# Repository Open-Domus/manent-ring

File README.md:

# Manent ring: hardware

Hardware design of the Manent ring: a ring with one button that records what you say
and hands it to your phone over Bluetooth LE. Firmware and radio protocol live in the
`mnemo-band` repository; the public description is the `manent-site` repository.

Public page: [manentlabs.it/en/](https://manentlabs.it/en/) (English), [manentlabs.it/](https://manentlabs.it/) (Italian).

Nothing here has been built or measured. This is a design on paper, checked by scripts.

| What | Where |
| --- | --- |
| Design document: requirements, architecture, decisions | [docs/design.md](docs/design.md) |
| Does it fit? Envelope, islands, cell, ring sizes | [docs/space-budget.md](docs/space-budget.md) |
| How long does it last? | [docs/power-budget.md](docs/power-budget.md) |
| How does it charge? Contacts, dock, why not wireless | [docs/charging.md](docs/charging.md) |
| What is unknown, and what would settle it | [docs/open-questions.md](docs/open-questions.md) |
| Parts with sizes and how far each is verified | [parts/parts.yaml](parts/parts.yaml) |
| Circuit, as data | [electrical/gen/design.py](electrical/gen/design.py) |
| Schematic (KiCad 10), PDF, netlist, bill of materials | `electrical/kicad/`, `electrical/out/` |
| Board: placed and routed (connectivity proof, not a fabrication layout) | `electrical/kicad/manent.kicad_pcb`, `electrical/out/board-*.svg` |
| Charging dock, printable, one per ring size | `mechanical/manent_mech/dock.py`, `mechanical/out/print-dock-*.stl` |
| Fit model, drawings, STEP, STL to 3D print | `mechanical/`, `mechanical/out/` |
| Quote request for a fabricator | [quote/request.md](quote/request.md); `make quote` builds the zip to send |

## Build

Needs `uv`, and either KiCad 10 or Docker (`docker pull kicad/kicad:10.0`).

```
make all        # schematic, board, checks, tests, fit report, drawings, budgets, STEP
make test       # tests only
make route      # route the board again from scratch (several minutes; it may not finish every time)
```

The schematic and the board are generated: edit `electrical/gen/design.py` and the fit
model, never the `.kicad_sch` or `.kicad_pcb` files.
Every pin carries a label with its net name instead of drawn wires. `make schematic` runs
KiCad's rule check and compares the netlist KiCad reads with the one in `design.py`.

## Licences

Following the proposal on the product site: hardware under CERN-OHL-S v2 (`LICENSE`),
documents under CC BY-SA 4.0 (`LICENSE-docs`). The licence of the scripts is not decided.

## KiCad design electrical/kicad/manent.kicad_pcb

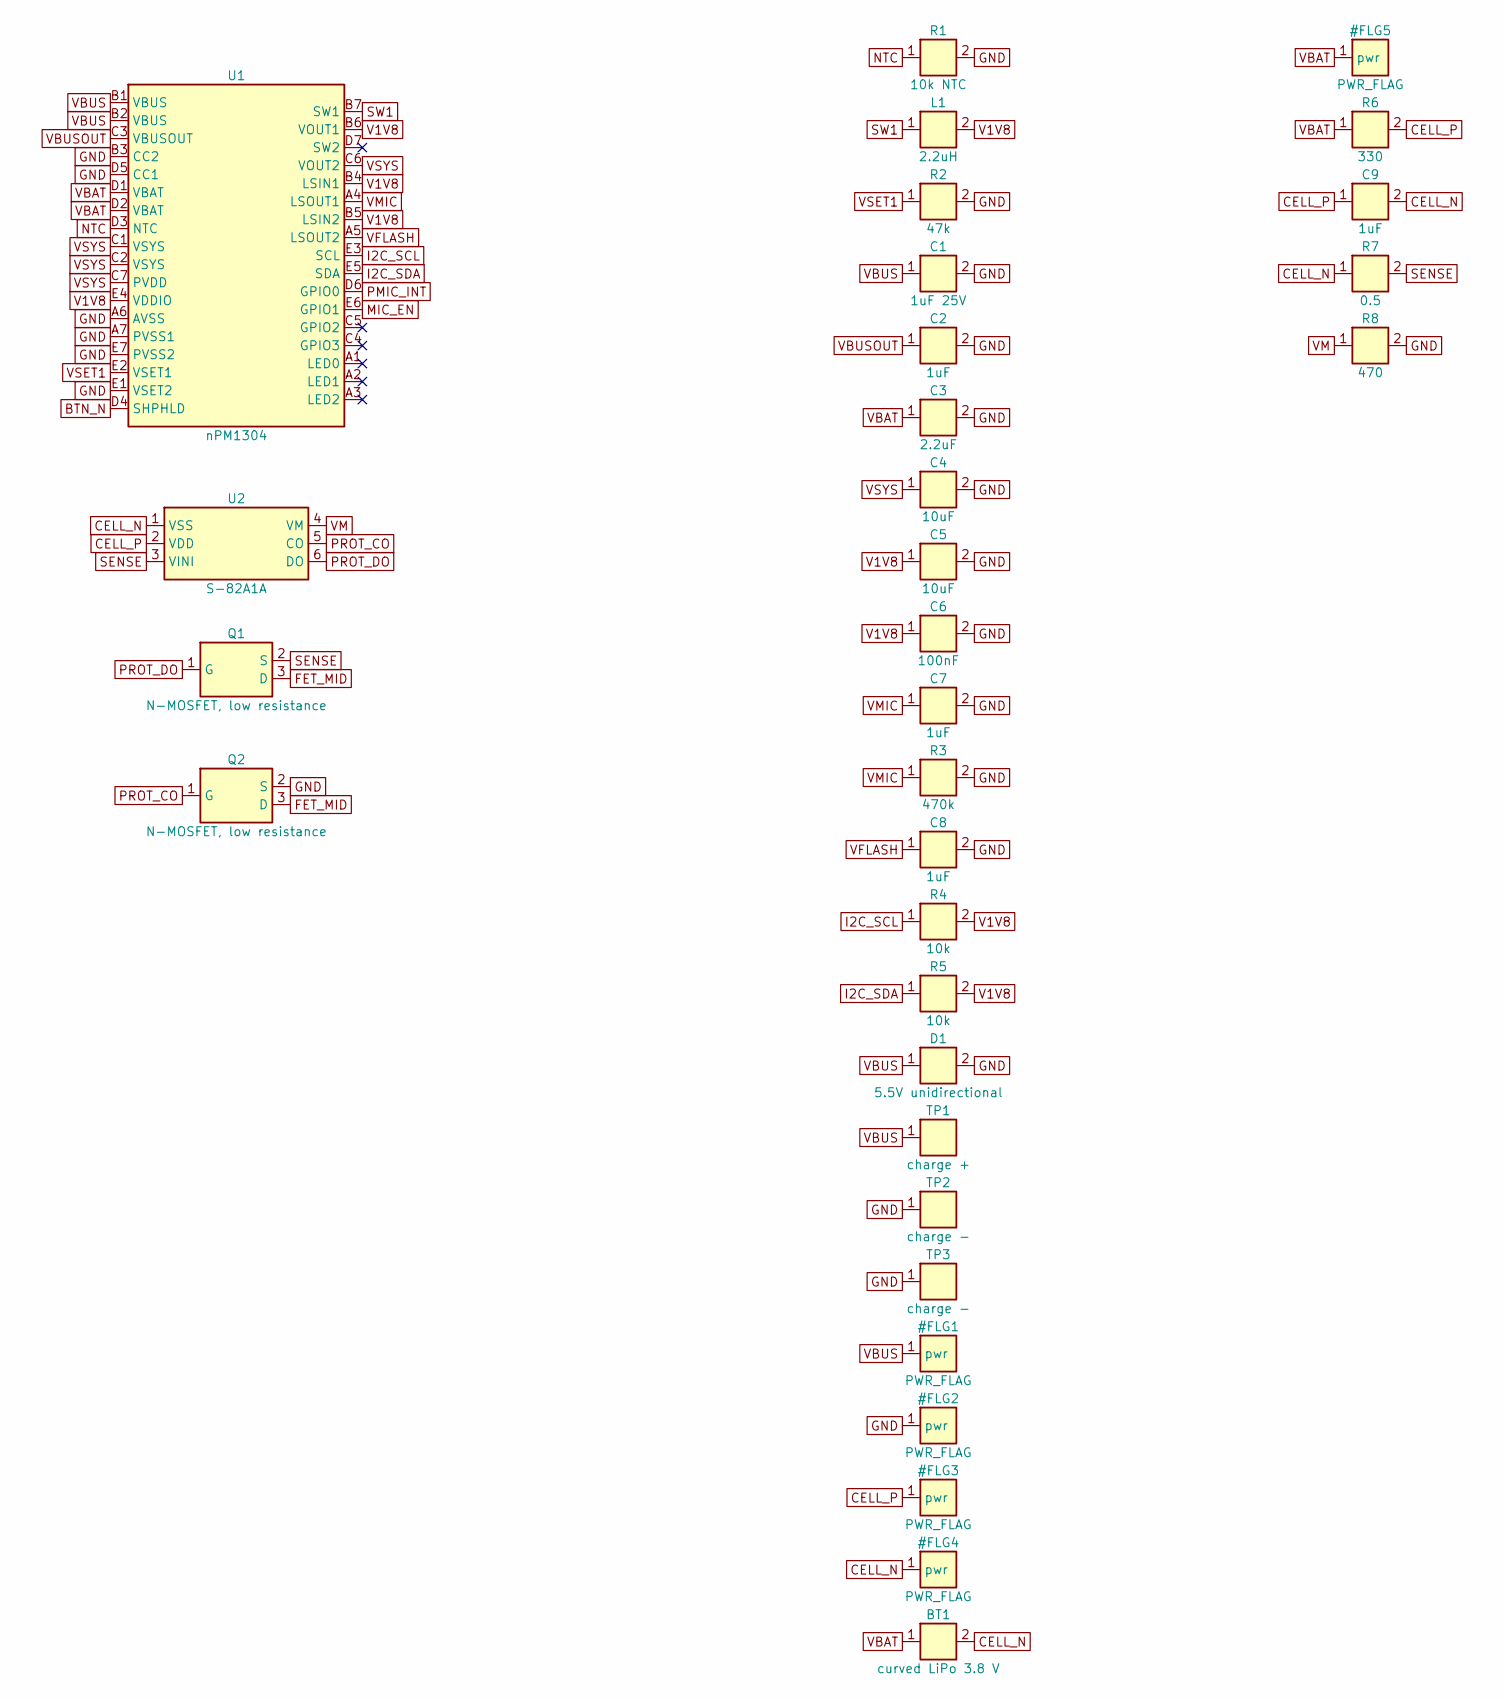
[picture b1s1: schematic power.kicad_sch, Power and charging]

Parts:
BT1: curved LiPo 3.8 V; Cell_Tabs; MPN GRP1707xx / GRP160626
C1: 1uF 25V; C_0402_1005Metric
C2, C7, C8, C9: 1uF; C_0201_0603Metric
C3: 2.2uF; C_0402_1005Metric
C4, C5: 10uF; C_0402_1005Metric
C6: 100nF; C_0201_0603Metric
D1: 5.5V unidirectional; D_0201_0603Metric; MPN to choose
L1: 2.2uH; L_0603_1608Metric; MPN to choose
Q1, Q2: N-MOSFET, low resistance; SOT-883; MPN PMZB290UNE2
R1: 10k NTC; R_0201_0603Metric
R2: 47k; R_0201_0603Metric
R3: 470k; R_0201_0603Metric
R4, R5: 10k; R_0201_0603Metric
R6: 330; R_0201_0603Metric
R7: 0.5; R_0201_0603Metric
R8: 470; R_0201_0603Metric
TP1: charge +; Pad_Charge_D1.5
TP2, TP3: charge -; Pad_Charge_D1.5
U1: nPM1304; nPM1304_CSP35; MPN nPM1304-CAAA-R
U2: S-82A1A; DFN-6_1414; MPN S-82A1AAG-A6T5S (variant to confirm)

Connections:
BTN_N: U1.D4 (SHPHLD); also elsewhere on the board
CELL_N: BT1.2, C9.2, R7.1, U2.1 (VSS)
CELL_P: C9.1, R6.2, U2.2 (VDD)
FET_MID: Q1.3 (D), Q2.3 (D)
GND: C1.2, C2.2, C3.2, C4.2, C5.2, C6.2, C7.2, C8.2, D1.2, Q2.2 (S), R1.2, R2.2, R3.2, R8.2, TP2.1, TP3.1, U1.A6 (AVSS), U1.A7 (PVSS1), U1.B3 (CC2), U1.D5 (CC1), U1.E1 (VSET2), U1.E7 (PVSS2); also elsewhere on the board
I2C_SCL: R4.1, U1.E3 (SCL); also elsewhere on the board
I2C_SDA: R5.1, U1.E5 (SDA); also elsewhere on the board
MIC_EN: U1.E6 (GPIO1); also elsewhere on the board
NTC: R1.1, U1.D3 (NTC)
PMIC_INT: U1.D6 (GPIO0); also elsewhere on the board
PROT_CO: Q2.1 (G), U2.5 (CO)
PROT_DO: Q1.1 (G), U2.6 (DO)
SENSE: Q1.2 (S), R7.2, U2.3 (VINI)
SW1: L1.1, U1.B7 (SW1)
V1V8: C5.1, C6.1, L1.2, R4.2, R5.2, U1.B4 (LSIN1), U1.B5 (LSIN2), U1.B6 (VOUT1), U1.E4 (VDDIO); also elsewhere on the board
VBAT: BT1.1, C3.1, R6.1, U1.D1 (VBAT), U1.D2 (VBAT); also elsewhere on the board
VBUS: C1.1, D1.1, TP1.1, U1.B1 (VBUS), U1.B2 (VBUS); also elsewhere on the board
VBUSOUT: C2.1, U1.C3 (VBUSOUT)
VFLASH: C8.1, U1.A5 (LSOUT2); also elsewhere on the board
VM: R8.1, U2.4 (VM)
VMIC: C7.1, R3.1, U1.A4 (LSOUT1); also elsewhere on the board
VSET1: R2.1, U1.E2 (VSET1)
VSYS: C4.1, U1.C1 (VSYS), U1.C2 (VSYS), U1.C6 (VOUT2), U1.C7 (PVDD); also elsewhere on the board

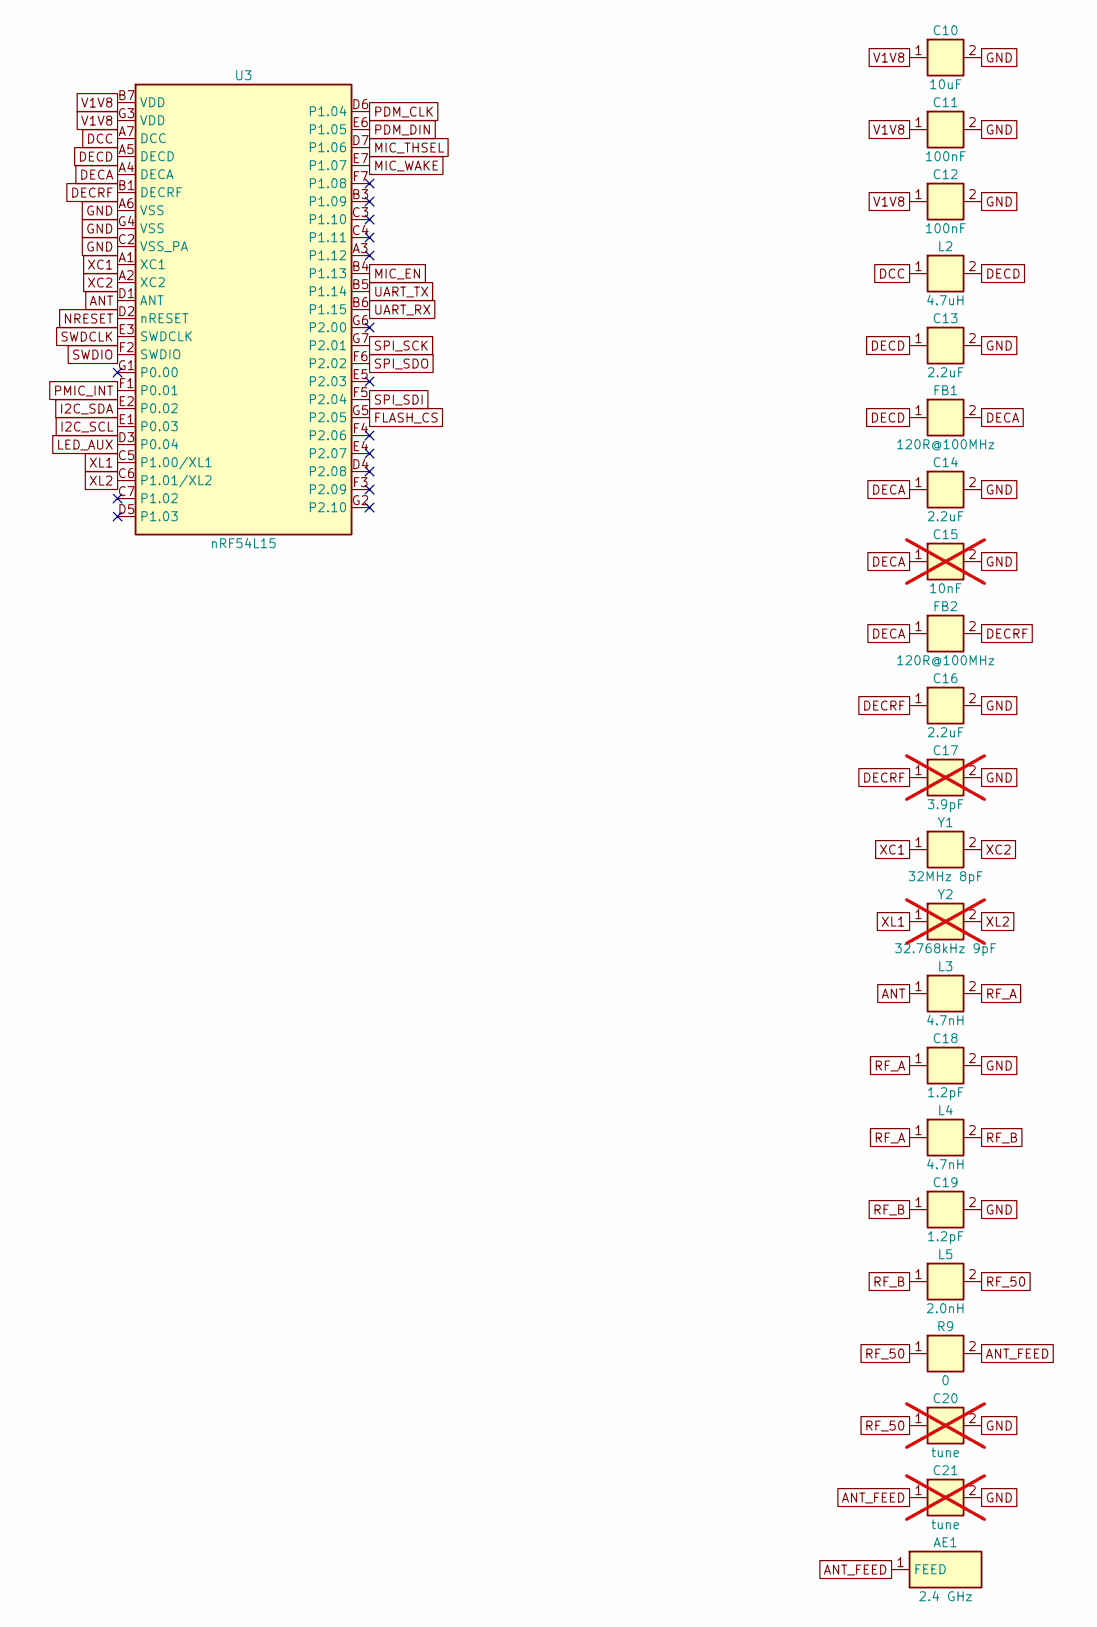
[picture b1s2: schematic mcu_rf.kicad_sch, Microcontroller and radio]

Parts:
AE1: 2.4 GHz; Antenna_1608; MPN ANT1608LL14R2400A
C10: 10uF; C_0402_1005Metric
C11, C12: 100nF; C_0201_0603Metric
C13, C14, C16: 2.2uF; C_0201_0603Metric; MPN GRM033R61A225KE47
C15: 10nF; C_0201_0603Metric; not fitted
C17: 3.9pF; C_0201_0603Metric; not fitted
C18, C19: 1.2pF; C_0201_0603Metric; MPN GJM0335C1H1R2WB01D
C20, C21: tune; C_0201_0603Metric; not fitted
FB1, FB2: 120R@100MHz; L_0201_0603Metric; MPN BLM03AG121SN1D
L2: 4.7uH; L_0402_1005Metric; MPN PLEA67BCA4R7M-1PT00
L3, L4: 4.7nH; L_0201_0603Metric; MPN LQP03HQ4N7H02
L5: 2.0nH; L_0201_0603Metric; MPN LQP03HQ2N0B02
R9: 0; R_0201_0603Metric
U3: nRF54L15; nRF54L15_CSP47; MPN nRF54L15-CAAA-R
Y1: 32MHz 8pF; Crystal_1612_4Pad; MPN CX1612DB32000D0WZRC3
Y2: 32.768kHz 9pF; Crystal_SMD_2012-2Pin_2.0x1.2mm; MPN 9HT11-32.768KDZC-T; not fitted

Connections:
ANT: L3.1, U3.D1 (ANT)
ANT_FEED: AE1.1, C21.1, R9.2
DCC: L2.1, U3.A7 (DCC)
DECA: C14.1, C15.1, FB1.2, FB2.1, U3.A4 (DECA)
DECD: C13.1, FB1.1, L2.2, U3.A5 (DECD)
DECRF: C16.1, C17.1, FB2.2, U3.B1 (DECRF)
FLASH_CS: U3.G5 (P2.05); also elsewhere on the board
GND: C10.2, C11.2, C12.2, C13.2, C14.2, C15.2, C16.2, C17.2, C18.2, C19.2, C20.2, C21.2, U3.A6 (VSS), U3.C2 (VSS_PA), U3.G4 (VSS); also elsewhere on the board
I2C_SCL: U3.E1 (P0.03); also elsewhere on the board
I2C_SDA: U3.E2 (P0.02); also elsewhere on the board
LED_AUX: U3.D3 (P0.04); also elsewhere on the board
MIC_EN: U3.B4 (P1.13); also elsewhere on the board
MIC_THSEL: U3.D7 (P1.06); also elsewhere on the board
MIC_WAKE: U3.E7 (P1.07); also elsewhere on the board
NRESET: U3.D2 (nRESET); also elsewhere on the board
PDM_CLK: U3.D6 (P1.04); also elsewhere on the board
PDM_DIN: U3.E6 (P1.05); also elsewhere on the board
PMIC_INT: U3.F1 (P0.01); also elsewhere on the board
RF_50: C20.1, L5.2, R9.1
RF_A: C18.1, L3.2, L4.1
RF_B: C19.1, L4.2, L5.1
SPI_SCK: U3.G7 (P2.01); also elsewhere on the board
SPI_SDI: U3.F5 (P2.04); also elsewhere on the board
SPI_SDO: U3.F6 (P2.02); also elsewhere on the board
SWDCLK: U3.E3 (SWDCLK); also elsewhere on the board
SWDIO: U3.F2 (SWDIO); also elsewhere on the board
UART_RX: U3.B6 (P1.15); also elsewhere on the board
UART_TX: U3.B5 (P1.14); also elsewhere on the board
V1V8: C10.1, C11.1, C12.1, U3.B7 (VDD), U3.G3 (VDD); also elsewhere on the board
XC1: U3.A1 (XC1), Y1.1
XC2: U3.A2 (XC2), Y1.2
XL1: U3.C5 (P1.00/XL1), Y2.1
XL2: U3.C6 (P1.01/XL2), Y2.2

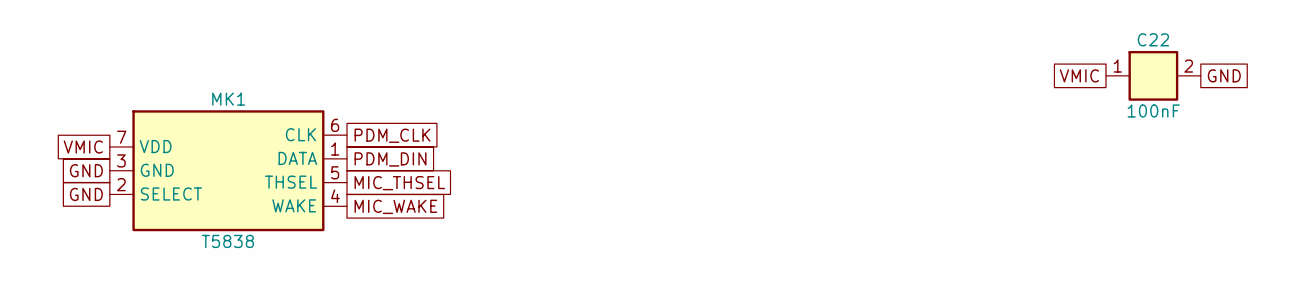
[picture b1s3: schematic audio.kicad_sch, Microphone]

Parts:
C22: 100nF; C_0201_0603Metric
MK1: T5838; MPN MMICT5838-00-012

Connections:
GND: C22.2, MK1.2 (SELECT), MK1.3 (GND); also elsewhere on the board
MIC_THSEL: MK1.5 (THSEL); also elsewhere on the board
MIC_WAKE: MK1.4 (WAKE); also elsewhere on the board
PDM_CLK: MK1.6 (CLK); also elsewhere on the board
PDM_DIN: MK1.1 (DATA); also elsewhere on the board
VMIC: C22.1, MK1.7 (VDD); also elsewhere on the board

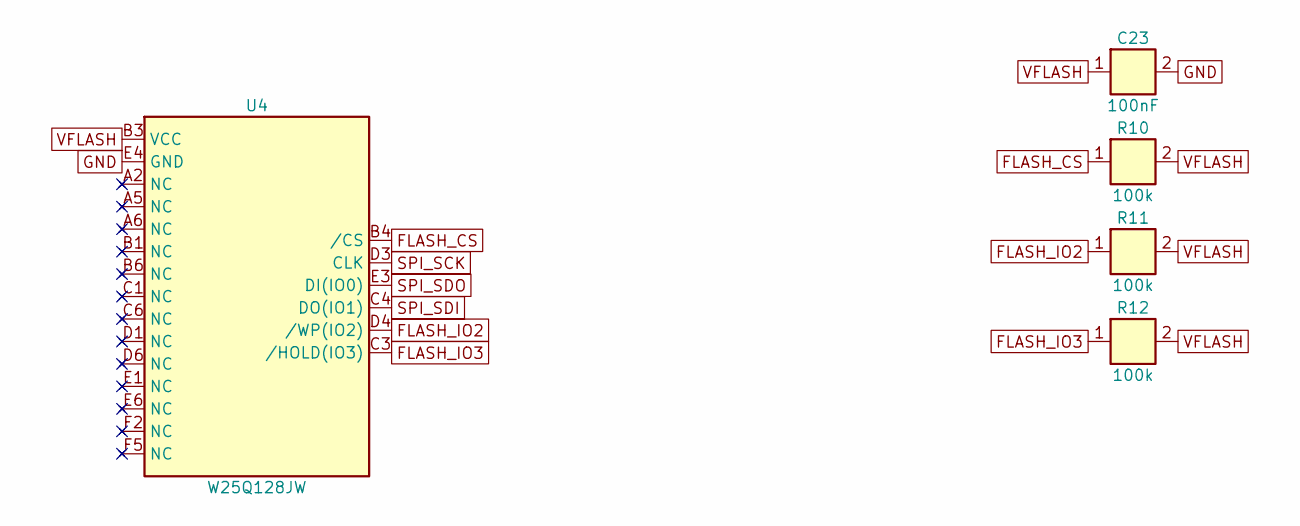
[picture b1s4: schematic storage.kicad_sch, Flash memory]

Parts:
C23: 100nF; C_0201_0603Metric
R10, R11, R12: 100k; R_0201_0603Metric
U4: W25Q128JW; W25Q128JW_WLCSP21; MPN W25Q128JWYIQ (or thin W25Q128JWKIQ)

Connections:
FLASH_CS: R10.1, U4.B4 (/CS); also elsewhere on the board
FLASH_IO2: R11.1, U4.D4 (/WP(IO2))
FLASH_IO3: R12.1, U4.C3 (/HOLD(IO3))
GND: C23.2, U4.E4 (GND); also elsewhere on the board
SPI_SCK: U4.D3 (CLK); also elsewhere on the board
SPI_SDI: U4.C4 (DO(IO1)); also elsewhere on the board
SPI_SDO: U4.E3 (DI(IO0)); also elsewhere on the board
VFLASH: C23.1, R10.2, R11.2, R12.2, U4.B3 (VCC); also elsewhere on the board

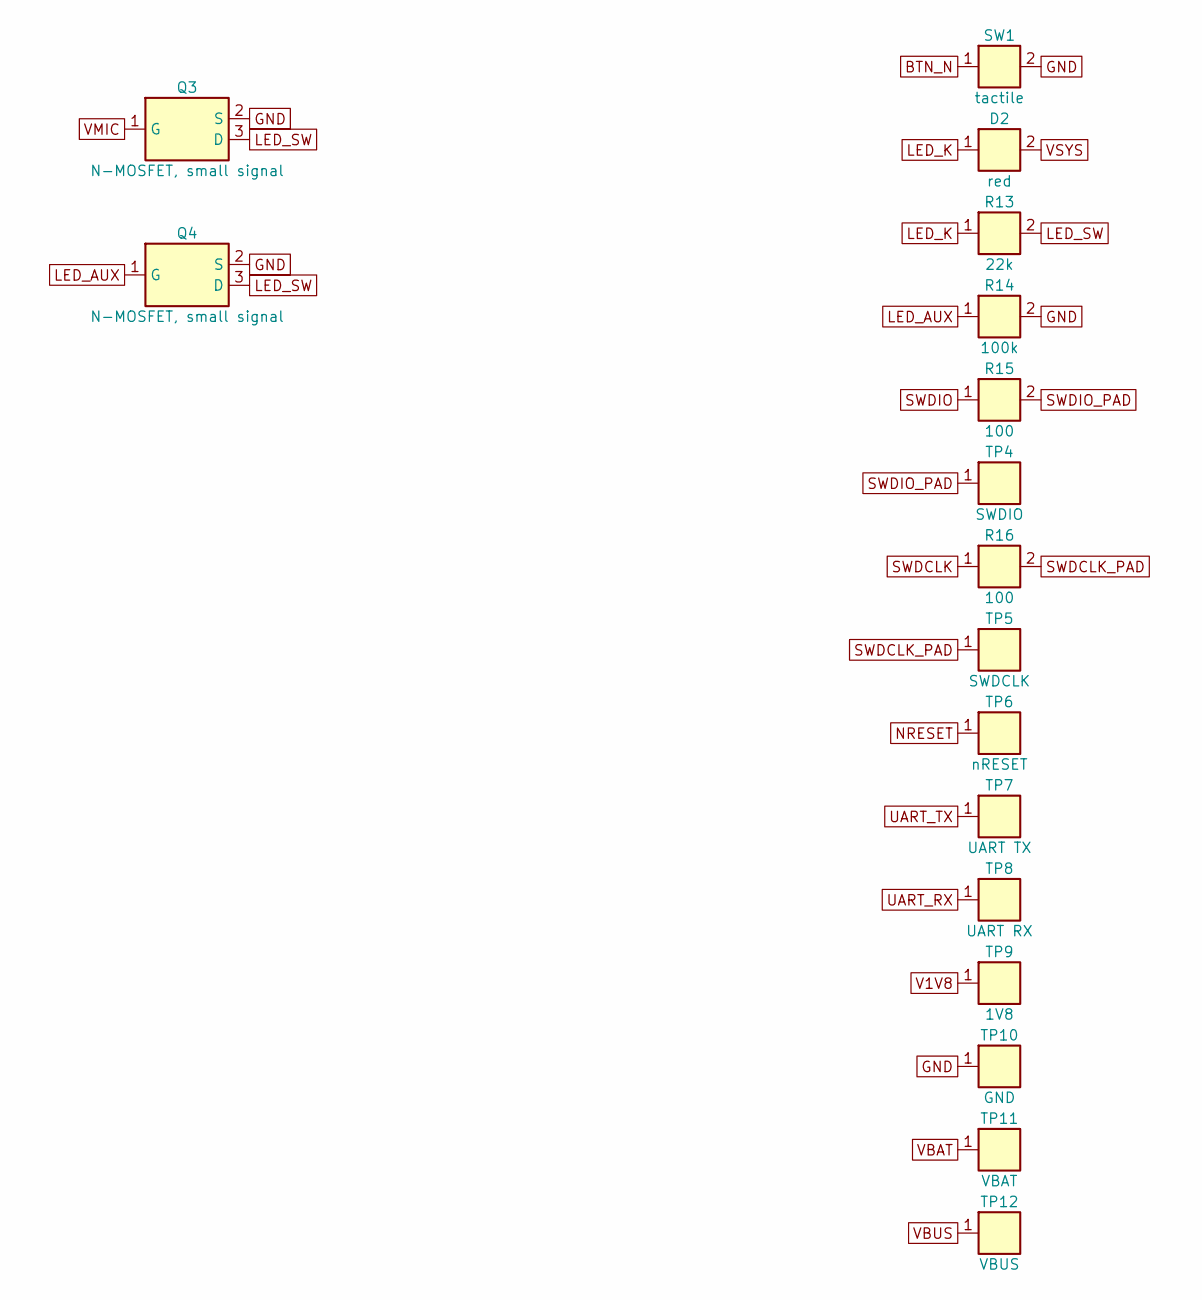
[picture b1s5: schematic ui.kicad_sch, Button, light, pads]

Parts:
D2: red; LED_0402_1005Metric; MPN SML-P11VT
Q3, Q4: N-MOSFET, small signal; SOT-883; MPN PMZB290UNE2
R13: 22k; R_0201_0603Metric
R14: 100k; R_0201_0603Metric
R15, R16: 100; R_0201_0603Metric
SW1: tactile; EVPBB; MPN EVPBB2A9B000
TP4: SWDIO; Pad_Service_D0.8
TP5: SWDCLK; Pad_Service_D0.8
TP6: nRESET; Pad_Test_D1.0
TP7: UART TX; Pad_Test_D1.0
TP8: UART RX; Pad_Test_D1.0
TP9: 1V8; Pad_Test_D1.0
TP10: GND; Pad_Test_D1.0
TP11: VBAT; Pad_Test_D1.0
TP12: VBUS; Pad_Test_D1.0

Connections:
BTN_N: SW1.1; also elsewhere on the board
GND: Q3.2 (S), Q4.2 (S), R14.2, SW1.2, TP10.1; also elsewhere on the board
LED_AUX: Q4.1 (G), R14.1; also elsewhere on the board
LED_K: D2.1, R13.1
LED_SW: Q3.3 (D), Q4.3 (D), R13.2
NRESET: TP6.1; also elsewhere on the board
SWDCLK: R16.1; also elsewhere on the board
SWDCLK_PAD: R16.2, TP5.1
SWDIO: R15.1; also elsewhere on the board
SWDIO_PAD: R15.2, TP4.1
UART_RX: TP8.1; also elsewhere on the board
UART_TX: TP7.1; also elsewhere on the board
V1V8: TP9.1; also elsewhere on the board
VBAT: TP11.1; also elsewhere on the board
VBUS: TP12.1; also elsewhere on the board
VMIC: Q3.1 (G); also elsewhere on the board
VSYS: D2.2; also elsewhere on the board

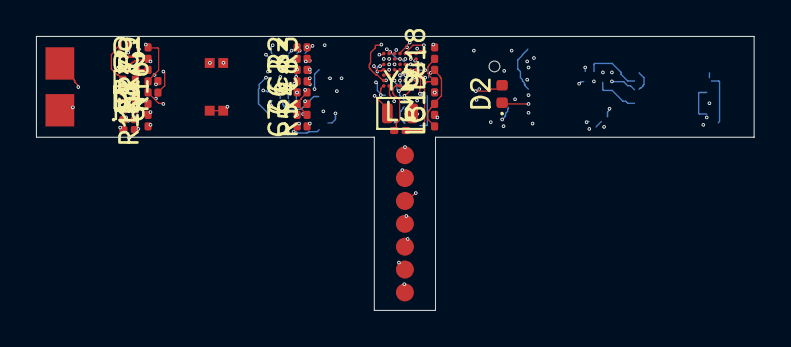
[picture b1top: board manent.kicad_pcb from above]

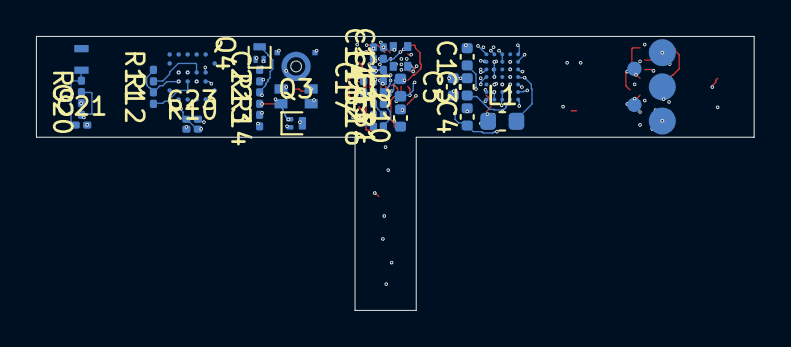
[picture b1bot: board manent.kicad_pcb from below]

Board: 6 copper layers, 39.9 x 15.2 mm, 74 parts (38 on the bottom side), 56 nets.

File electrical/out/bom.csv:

References,Quantity,Value,Manufacturer,Part number,Package,Fitted,Notes
U1,1,nPM1304,Nordic Semiconductor,nPM1304-CAAA-R,WLCSP-35,yes,"BUCK2 unused as in Nordic's reference configuration 2: VSET2 grounded, SW2 open, VOUT2 to VSYS. LED0-2, GPIO2-3 left open"
R1,1,10k NTC,,,0201,yes,"Thermistor, to sit against the cell: stops charging when hot or cold"
L1,1,2.2uH,,to choose,0603,yes,"DCR <= 0.4 ohm, Isat > 350 mA; part and height to choose"
R2,1,47k,,,0201,yes,Sets BUCK1 to 1.8 V at power-on
C1,1,1uF 25V,,,0402,yes,"As Nordic's nPM1304 reference layout 1.0, configuration 2"
C2 C7 C8 C9,4,1uF,,,0201,yes,"As Nordic's nPM1304 reference layout 1.0, configuration 2 | Load switch output. As Nordic's nPM1304 reference layout 1.0, configuration 2 | With the 330 ohm: at least 100 uF x ohm, as the protector asks"
C3,1,2.2uF,,,0402,yes,"As Nordic's nPM1304 reference layout 1.0, configuration 2 (2.2 uF X7R 16 V in 0603 there)"
C4 C5 C10,3,10uF,,,0402,yes,"Buck input, at PVDD and PVSS1. The reference has a second 10 uF on VSYS; the ring has no room for it | Buck output: at least 4 uF effective. As Nordic's nPM1304 reference layout 1.0, configuration 2"
C6 C11 C12 C22 C23,5,100nF,,,0201,yes,"VDDIO | X7R, next to pin 7"
R3,1,470k,,,0201,yes,"Empties the rail when the switch opens, so the light goes out with the microphone"
R4 R5,2,10k,,,0201,yes,
D1,1,5.5V unidirectional,,to choose,0201,yes,"Pin 1 is the cathode. Unidirectional, so that a negative strike is clamped near -0.7 V"
BT1,1,curved LiPo 3.8 V,Grepow,GRP1707xx / GRP160626,,yes,Capacity depends on ring size; see docs/space-budget.md
R6,1,330,,,0201,yes,Protector supply filter
U2,1,S-82A1A,ABLIC,S-82A1AAG-A6T5S (variant to confirm),DFN-6 1.4x1.4,yes,"Fit only if the cell has no protection of its own. This variant trips at 4.23 V: right for a 4.20 V cell with little margin, wrong for a 4.35 V one. Choose with the cell"
R7,1,0.5,,,0201,yes,Overcurrent sense: trips at 100 mA out and 60 mA in (50 mV and 30 mV thresholds); to check against peaks
R8,1,470,,,0201,yes,
Q1 Q2,2,"N-MOSFET, low resistance",Nexperia,PMZB290UNE2,DFN1006B-3,yes,Discharge FET; carries the cell current | Charge FET; carries the cell current
U3,1,nRF54L15,Nordic Semiconductor,nRF54L15-CAAA-R,"WLCSP-47, 0.3 mm pitch",yes,Light-sensitive package: the resin around it must be opaque
L2,1,4.7uH,TDK,PLEA67BCA4R7M-1PT00,0402,yes,
C13 C14 C16,3,2.2uF,Murata,GRM033R61A225KE47,0201,yes,
FB1 FB2,2,120R@100MHz,Murata,BLM03AG121SN1D,0201,yes,
C15,1,10nF,,,0201,no,Not fitted in Nordic's reference
C17,1,3.9pF,,,0201,no,Not fitted in Nordic's reference
Y1,1,32MHz 8pF,Kyocera,CX1612DB32000D0WZRC3,1612,yes,Load capacitors are inside the chip
Y2,1,32.768kHz 9pF,TXC,9HT11-32.768KDZC-T,2012,no,Optional: start on the internal RC oscillator
L3 L4,2,4.7nH,Murata,LQP03HQ4N7H02,0201,yes,
C18 C19,2,1.2pF,Murata,GJM0335C1H1R2WB01D,0201,yes,
L5,1,2.0nH,Murata,LQP03HQ2N0B02,0201,yes,
R9,1,0,,,0201,yes,"Antenna tuning, series: value from measurement on a potted ring"
C20 C21,2,tune,,,0201,no,"Antenna tuning, shunt"
AE1,1,2.4 GHz,Yageo,ANT1608LL14R2400A,,yes,Chip antenna or printed trace at the band edge; decided with the first radio measurements
MK1,1,T5838,TDK InvenSense,MMICT5838-00-012,3.5x2.65x0.98 bottom port,yes,No pull resistor on DATA. Board hole 0.5-1.0 mm under the port
U4,1,W25Q128JW,Winbond,W25Q128JWYIQ (or thin W25Q128JWKIQ),"WLCSP-21, 0.5 mm pitch",yes,"Special-order package; body size not published, ask Winbond"
R10 R11 R12 R14,4,100k,,,0201,yes,Keeps the chip deselected while the rail rises | Termination in single-bit SPI not stated in the datasheet | Light off while the SoC is in reset
SW1,1,tactile,Panasonic,EVPBB2A9B000,2.6x1.6x0.53,yes,1.6 N; pulled up inside the PMIC (SHPHLD). The SoC learns of presses from the PMIC interrupt
D2,1,red,Rohm,SML-P11VT,1.0x0.6x0.2,yes,Pin 1 is the cathode. For the wearer only: about 0.1 mA
R13,1,22k,,,0201,yes,About 0.06-0.11 mA over the cell voltage; adjust after a look through the resin
Q3 Q4,2,"N-MOSFET, small signal",Nexperia,PMZB290UNE2,DFN1006B-3,yes,Gate is the microphone rail: the light is on whenever the microphone has power. Vgs(th) under 1 V | Lets firmware blink the light for errors and charging
R15 R16,2,100,,,0201,yes,Between the chip and a pad that touches the skin

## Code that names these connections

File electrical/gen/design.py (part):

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SW = two_pin("SW", "SW")
CELL = two_pin("CELL", "BT")
PAD = SymDef("PAD", "TP", (Pin("1", "~", "passive", "L"),), width=5.08)
ANT = SymDef("ANTENNA", "AE", (Pin("1", "FEED", "passive", "L"),), width=10.16)
FLAG = SymDef("PWR_FLAG", "#FLG", (Pin("1", "pwr", "power_out", "L"),), width=5.08, virtual=True)
NFET = ic("NMOS", "Q", "1 G i L\n2 S p R\n3 D p R", width=10.16)

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A5 LSOUT2 po R
E3 SCL i R
E5 SDA b R
D6 GPIO0 b R
E6 GPIO1 b R
C5 GPIO2 b R
C4 GPIO3 b R
A1 LED0 p R
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        "VSYS": "VSYS", "PVDD": "VSYS", "VDDIO": "V1V8", "AVSS": "GND", "PVSS1": "GND", "PVSS2": "GND",
        "VSET1": "VSET1", "VSET2": "GND", "SHPHLD": "BTN_N", "SW1": "SW1", "VOUT1": "V1V8",
        "VOUT2": "VSYS", "LSIN1": "V1V8", "LSOUT1": "VMIC", "LSIN2": "V1V8", "LSOUT2": "VFLASH",
        "SCL": "I2C_SCL", "SDA": "I2C_SDA", "GPIO0": "PMIC_INT", "GPIO1": "MIC_EN",
    }), mpn="nPM1304-CAAA-R", mfr="Nordic Semiconductor", package="WLCSP-35",
        note="BUCK2 unused as in Nordic's reference configuration 2: VSET2 grounded, SW2 open, VOUT2 to VSYS. "
             "LED0-2, GPIO2-3 left open")
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                                             "DATA": "PDM_DIN", "THSEL": "MIC_THSEL", "WAKE": "MIC_WAKE"}),
        mpn="MMICT5838-00-012", mfr="TDK InvenSense", package="3.5x2.65x0.98 bottom port",
        note="No pull resistor on DATA. Board hole 0.5-1.0 mm under the port")
    cap("100nF", "VMIC", "audio", note="X7R, next to pin 7")

    # ---- flash ---------------------------------------------------------------------
    add(FLASH, "W25Q128JW", "storage", by_name(FLASH, {
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    add(NFET, "N-MOSFET, small signal", "ui", {"1": "LED_AUX", "2": "GND", "3": "LED_SW"}, mpn="PMZB290UNE2", mfr="Nexperia", package="DFN1006B-3",
        note="Lets firmware blink the light for errors and charging")
    res("100k", "LED_AUX", "GND", "ui", note="Light off while the SoC is in reset")
    for label, net in (("SWDIO", "SWDIO"), ("SWDCLK", "SWDCLK")):
        res("100", net, net + "_PAD", "ui", note="Between the chip and a pad that touches the skin")
        add(PAD, label, "ui", (net + "_PAD",), note="Service pad on the inner surface: reachable after potting")
    for label, net in (("nRESET", "NRESET"), ("UART TX", "UART_TX"), ("UART RX", "UART_RX"), ("1V8", "V1V8"),
                       ("GND", "GND"), ("VBAT", "VBAT"), ("VBUS", "VBUS")):
        add(PAD, label, "ui", (net,), note="Test tail, cut off before potting")
    for c in comps:
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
